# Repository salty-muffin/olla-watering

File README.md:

# olla-watering
automatic olla filling with a rp pico, valves &amp; sensors

# plan

JSON on every Pico that contains: 
- time slot, when the watering program shall be started
- maximum filling for each valve
- overfill time in seconds (time the valve stays open after the sensor registers `full`)

# filling program
For each Valve 
- average sensor signal over X seconds (long) to estimate if the olla really needs filling
- after valve is opened, a shorter peridod of time is used to estimate the new `full` state
- then the valve stays open for X seconds, as set in the JSON to ensure the sensor will not register an empty olla too soon.

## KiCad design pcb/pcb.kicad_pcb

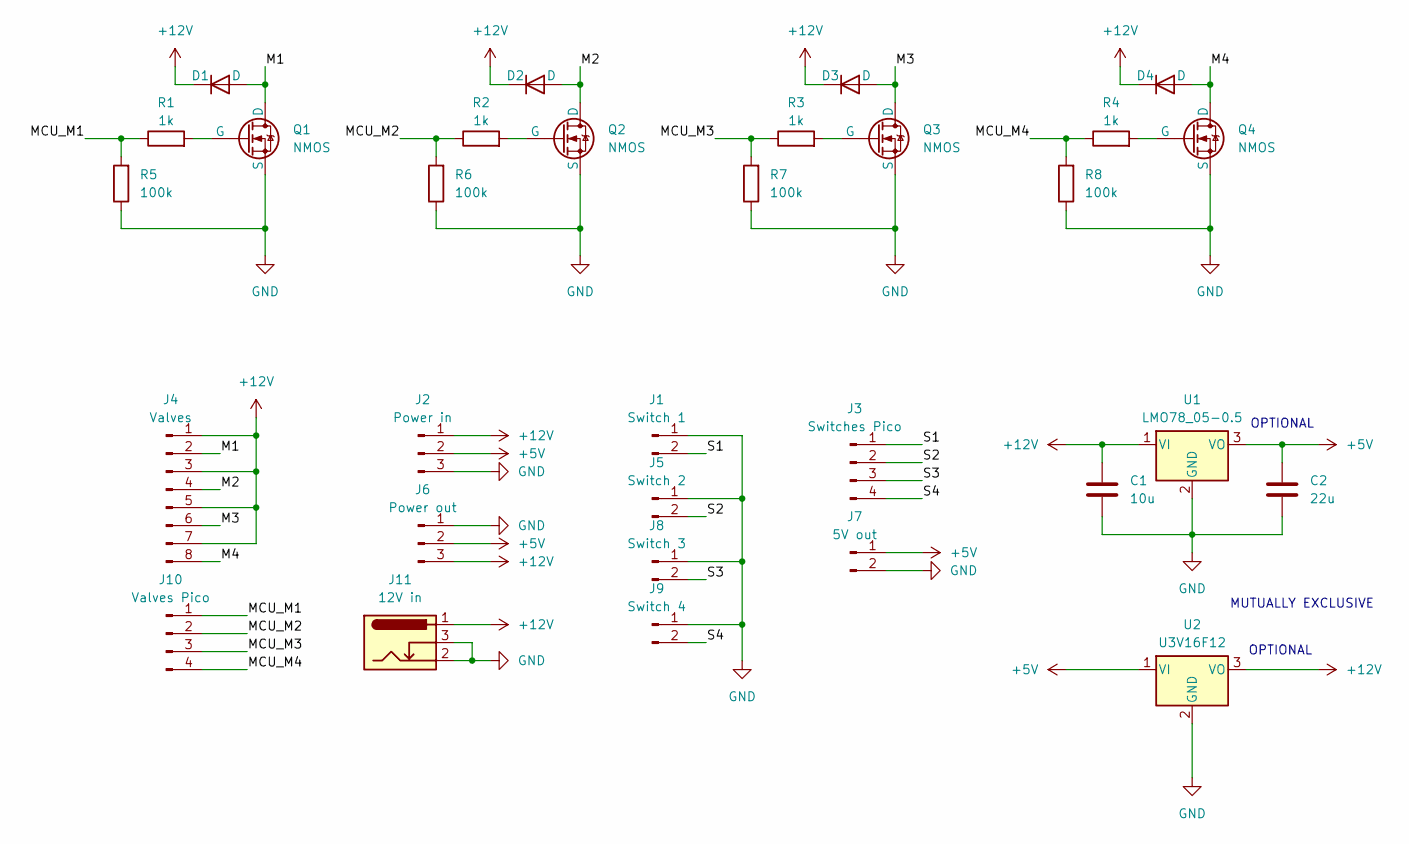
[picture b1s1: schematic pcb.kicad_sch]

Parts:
C1: 10u; C_1206_3216Metric_Pad1.33x1.80mm_HandSolder
C2: 22u; C_1206_3216Metric_Pad1.33x1.80mm_HandSolder
D1, D2, D3, D4: D; D_DO-41_SOD81_P10.16mm_Horizontal
J1: Switch 1; PinHeader_1x02_P2.54mm_Vertical
J2: Power in; TerminalBlock_4Ucon_1x03_P3.50mm_Horizontal
J3: Switches Pico; PinHeader_1x04_P2.54mm_Vertical
J4: Valves; JST_XH_B8B-XH-A_1x08_P2.50mm_Vertical
J5: Switch 2; PinHeader_1x02_P2.54mm_Vertical
J6: Power out; TerminalBlock_4Ucon_1x03_P3.50mm_Horizontal
J7: 5V out; PinHeader_1x02_P2.54mm_Vertical
J8: Switch 3; PinHeader_1x02_P2.54mm_Vertical
J9: Switch 4; PinHeader_1x02_P2.54mm_Vertical
J10: Valves Pico; PinHeader_1x04_P2.54mm_Vertical
J11: 12V in; BarrelJack_Wuerth_6941xx301002
Q1, Q2, Q3, Q4: NMOS; TO-220-3_Vertical_olla
R1, R2, R3, R4: 1k; R_Axial_DIN0207_L6.3mm_D2.5mm_P7.62mm_Horizontal
R5, R6, R7, R8: 100k; R_Axial_DIN0207_L6.3mm_D2.5mm_P7.62mm_Horizontal
U1: LMO78_05-0.5
U2: U3V16F12

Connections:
+5V: C2.1, J2.2, J6.2, J7.1, U1.3 (VO), U2.1 (VI)
+12V: C1.1, D1.1 (K), D2.1 (K), D3.1 (K), D4.1 (K), J2.1, J4.1, J4.3, J4.5, J4.7, J6.3, J11.1, U1.1 (VI), U2.3 (VO)
/M1: D1.2 (A), J4.2, Q1.1 (D)
/M2: D2.2 (A), J4.4, Q2.1 (D)
/M3: D3.2 (A), J4.6, Q3.1 (D)
/M4: D4.2 (A), J4.8, Q4.1 (D)
/MCU_M1: J10.1, R1.1, R5.2
/MCU_M2: J10.2, R2.1, R6.2
/MCU_M3: J10.3, R3.1, R7.2
/MCU_M4: J10.4, R4.1, R8.2
/S1: J1.2, J3.1
/S2: J3.2, J5.2
/S3: J3.3, J8.2
/S4: J3.4, J9.2
GND: C1.2, C2.2, J1.1, J2.3, J5.1, J6.1, J7.2, J8.1, J9.1, J11.2, J11.3, Q1.3 (S), Q2.3 (S), Q3.3 (S), Q4.3 (S), R5.1, R6.1, R7.1, R8.1, U1.2 (GND), U2.2 (GND)
unnamed: Q1.2 (G), R1.2
unnamed: Q2.2 (G), R2.2
unnamed: Q3.2 (G), R3.2
unnamed: Q4.2 (G), R4.2

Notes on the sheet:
OPTIONAL
MUTUALLY EXCLUSIVE

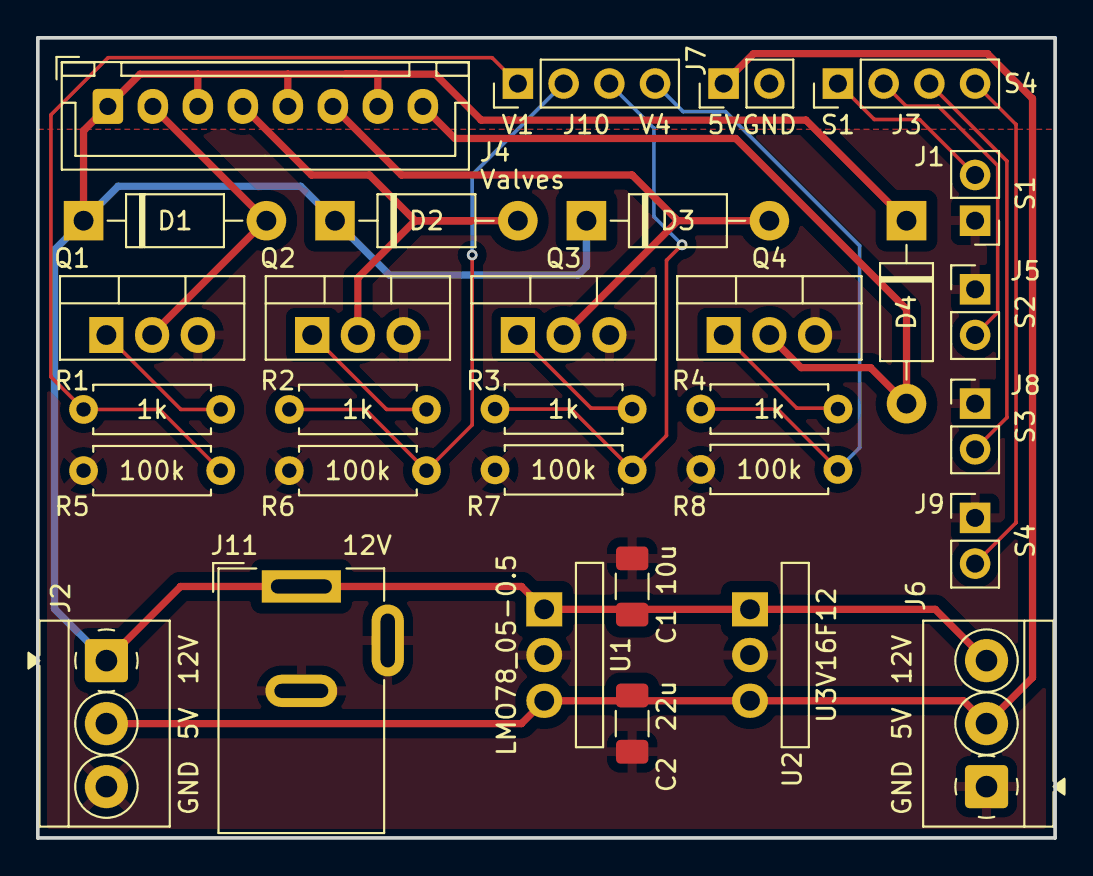
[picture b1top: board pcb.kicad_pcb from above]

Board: 2 copper layers, 56.5 x 44.4 mm, 31 parts (0 on the bottom side), 19 nets.

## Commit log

2025-03-07 first pcb design
2025-03-07 finished board
2025-03-07 added leaf
2025-03-29 initialize project structure with configuration for micropython
2025-04-23 refactor: update switch condition to improve readability
2025-04-23 added json
2025-04-23 feat: implement Swimmer class for water level detection with sensor readings
2025-04-23 feat: add Pin class for GPIO control with on/off methods as a dummy
2025-04-23 feat: add reset method to Swimmer class for state management
2025-04-23 add pin_number attribute in Swimmer class constructor
2025-04-23 added pin_number
2025-04-23 first iteration main watering script
2025-04-23 Fix time slot check and improve swimmer sensor logic; refactor mean calculation in Swimmer class
2025-04-29 finalized pcb design
2025-04-29 first error free version (so far)
2025-04-30 fixed fatal error: valves not closing when stopping due to max fill time reached
2025-05-01 last fixes
2025-05-01 update settings.json to increase max fill time and reduce overfill time per valve
2025-05-06 reduced cpu frequency and implemented lightsleep to reduce power consumtion
2025-05-09 Revert "Merge pull request #2 from salty-muffin/less-power"
    This reverts commit d77fe27bbbebd9265bdda4816e5cc27d5ede3d6a, reversing
    changes made to bab276253b1ad47a92121fc09bd17e3b1b6c4d56.
2025-05-09 Refactor main.py to improve logging and RTC initialization; added timestamped logging and removed redundant code.
2025-05-09 Revert "Refactor main.py to improve logging and RTC initialization; added timestamped logging and removed redundant code."
    This reverts commit b4701d842b13b28ac4a88064fd5fc5d61f346008.
2025-05-09 added timestamped logging & underclocked the cpu
2025-05-15 Fix: started with a higher sequence index to avoid wrong starting message
2025-05-15 Refactor main.py to encapsulate fill sensor logic in a dedicated function and improve readability.
2025-05-15 Only checking sensors now, when in sequence
2025-05-16 Add lightsleep to main loop
